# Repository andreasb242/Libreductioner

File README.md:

# Libreductioner
Induction loop sender for mower.

Tested and working with Landroid Worx. All Bugs in the Board are corrected with Version 1.1, all additional, no-needed Parts are removed.

# Forum Thread
Mikrocontroller.net: https://www.mikrocontroller.net/topic/451337 (German)

# Extension / Support for other mower
If you have another mower, or would like to improve the Board: Create a Pull request!

## Board / Circuit
The Board / Circuit is created with KiCad.

## Supported Mower
Currently working is the Landroid Worx

## Measuring
The Signal can be measured with a coil of a 24V Relais

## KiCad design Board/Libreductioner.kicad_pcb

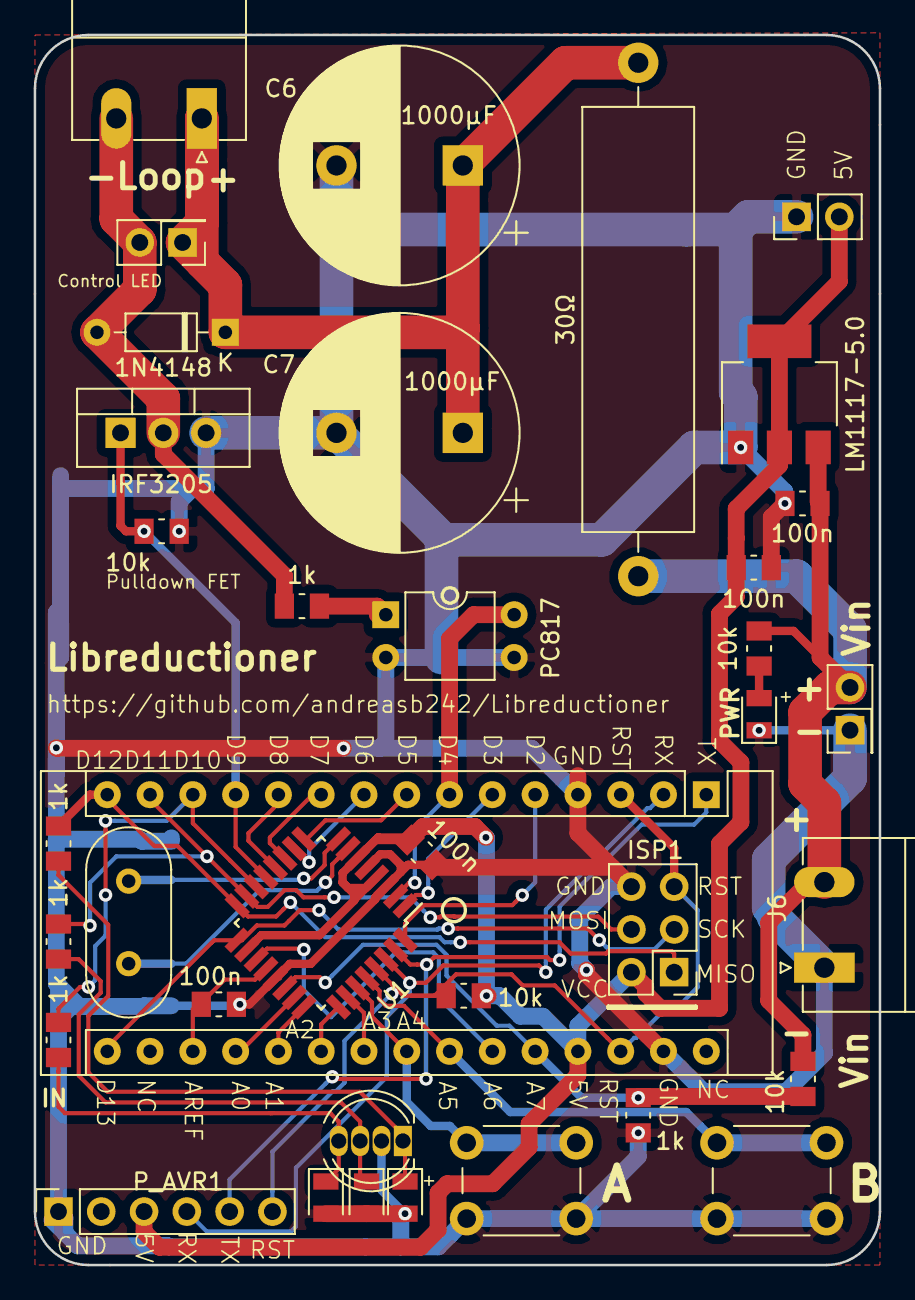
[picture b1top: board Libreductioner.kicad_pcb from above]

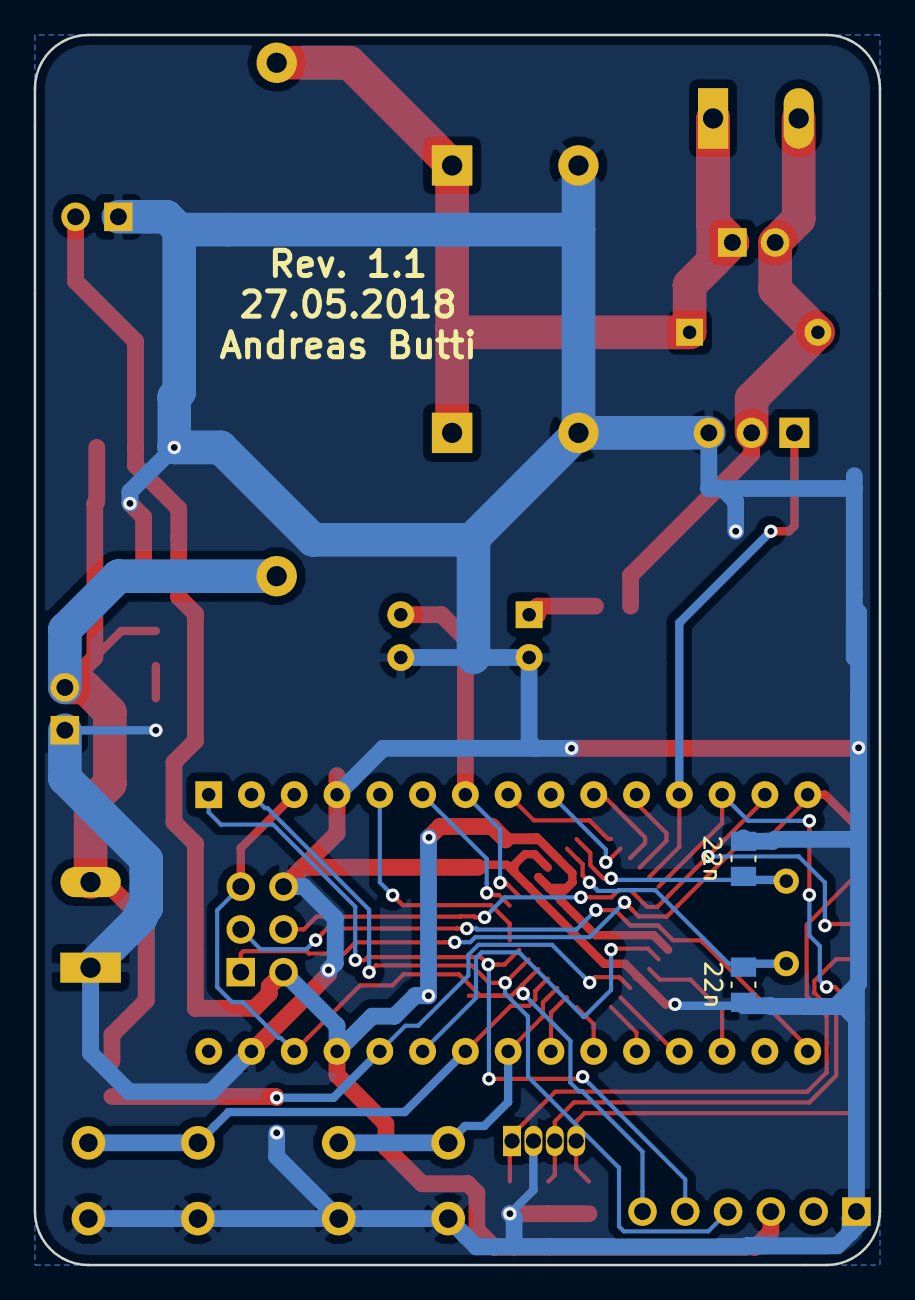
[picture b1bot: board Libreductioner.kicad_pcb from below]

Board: 2 copper layers, 50.2 x 73.0 mm, 39 parts (2 on the bottom side), 36 nets.

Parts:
A1: Arduino_Nano_v3.x; Arduino_Nano
C2, C3, C8, C9: 100n; C_0805_2012Metric_Pad1.15x1.50mm_HandSolder
C4, C5: 22n; C_0805_2012Metric_Pad1.15x1.50mm_HandSolder
C6, C7: 1000µF; CP_Radial_D14.0mm_P7.50mm
D1: LED_RCGB; LED_D5.0mm-4
D2: 1N4148; D_DO-35_SOD27_P7.62mm_Horizontal
D3, D4, D5, D6: LED; LED_0805_2012Metric_Pad0.97x1.50mm_HandSolder
ISP1: AVR-ISP-6; Pin_Header_Straight_2x03_Pitch2.54mm
J1, J2: Conn_01x02_Male; PinHeader_2x01_P2.54mm_Vertical
J4: Conn_01x02_Male; PinHeader_1x02_P2.54mm_Vertical
J5, J6: Conn_01x02_Male; PhoenixContact_MC_1,5_2-G-5.08_1x02_P5.08mm_Horizontal
P_AVR1: Conn_01x06_Female; PinSocket_1x06_P2.54mm_Vertical
Q1: IRF3205; TO-220-3_Vertical
R3: 30Ω; R_Axial_Power_L25.0mm_W6.4mm_P30.48mm
R5, R8, R16, R17, R18: 1k; R_0805_2012Metric_Pad1.15x1.50mm_HandSolder
R6, R7, R10, R11: 10k; R_0805_2012Metric_Pad1.15x1.50mm_HandSolder
SW_DOWN1: SW_Push; SW_PUSH_6mm_H8.5mm
SW_UP1: SW_Push; SW_PUSH_6mm_H8.5mm
U1: ATMEGA168A-AU; TQFP-32_7x7mm_P0.8mm
U3: PC817; DIP-4_W7.62mm
U4: LM1117-5.0; SOT-223-3_TabPin2
Y1: Crystal; Crystal_HC18-U_Vertical

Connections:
+12V: C9.1, J2.2, J6.2, R3.1, R7.1, R11.1, U4.3
/A0: A1.19, U1.23
/A1: A1.20, U1.24
/A2: A1.21, U1.25
/A3: A1.22, U1.26
/A4: A1.23, SW_DOWN1.2, U1.27
/A5: A1.24, SW_UP1.2, U1.28
/A6: A1.25, U1.19
/A7: A1.26, R7.2, R8.1, U1.22
/AREF: A1.18, C3.1, U1.20
/BUFFERED12V: C6.1, C7.1, D2.1, J1.1, J5.1, R3.2
/D0/RX: A1.2, P_AVR1.4, U1.30
/D1/TX: A1.1, P_AVR1.5, U1.31
/D2: A1.5, U1.32
/D3: A1.6, U1.1
/D4: A1.7, U1.2, U3.4
/D5: A1.8, U1.9
/D6: A1.9, U1.10
/D7: A1.10, U1.11
/D8: A1.11, U1.12
/D9: A1.12, Q1.1, R6.1, U1.13
/D10: A1.13, R18.1, U1.14
/D11/MOSI: A1.14, ISP1.4, R17.1, U1.15
/D12/MISO: A1.15, ISP1.1, R16.1, U1.16
/D13/SCK: A1.16, ISP1.3, U1.17
/RESET: A1.3, A1.28, ISP1.5, P_AVR1.6, R10.2, U1.29
GND: A1.4, A1.29, C2.2, C3.2, C4.1, C5.1, C6.2, C7.2, C8.2, C9.2, D1.2, D3.2, D4.1, D5.2, D6.2, ISP1.6, J2.1, J4.1, J6.1, P_AVR1.1, Q1.3, R6.2, R8.2, SW_DOWN1.1, SW_UP1.1, U1.3, U1.5, U1.21, U3.2, U3.3, U4.1
unnamed: C4.2, U1.7, Y1.1
unnamed: C5.2, U1.8, Y1.2
unnamed: D1.1, D5.1, R16.2
unnamed: D1.3, D6.1, R17.2
unnamed: D1.4, D3.1, R18.2
unnamed: D2.2, J1.2, J5.2, Q1.2, R5.2
unnamed: D4.2, R11.2
unnamed: R5.1, U3.1
VCC: A1.27, C2.1, C8.1, ISP1.2, J4.2, P_AVR1.3, R10.1, U1.4, U1.6, U1.18, U4.2

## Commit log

2018-05-12 Board
2018-05-12 Added Images
2018-05-12 Added Screenshots / Source
2018-05-13 Board optimized
2018-05-13 Board optimisations
2018-05-13 Optimized Board
2018-05-13 Improved Board
2018-05-13 Added gerber files for production
2018-05-22 Pinout adapted to board
2018-05-22 Fixed wrong description on Power Plug
2018-05-26 Firmware
2018-05-26 Fixed layout bugs found on Testing
2018-05-26 Software
2018-05-27 Board Cleanup, removed all non-needed parts
2018-05-27 Updated Board Screenshots
2018-05-27 Tested & Working
2018-05-27 Added forum link
2018-05-28 Menu, Manual.
2018-05-28 Removed Input: AVR is to slow for measuring the signal precise enough
